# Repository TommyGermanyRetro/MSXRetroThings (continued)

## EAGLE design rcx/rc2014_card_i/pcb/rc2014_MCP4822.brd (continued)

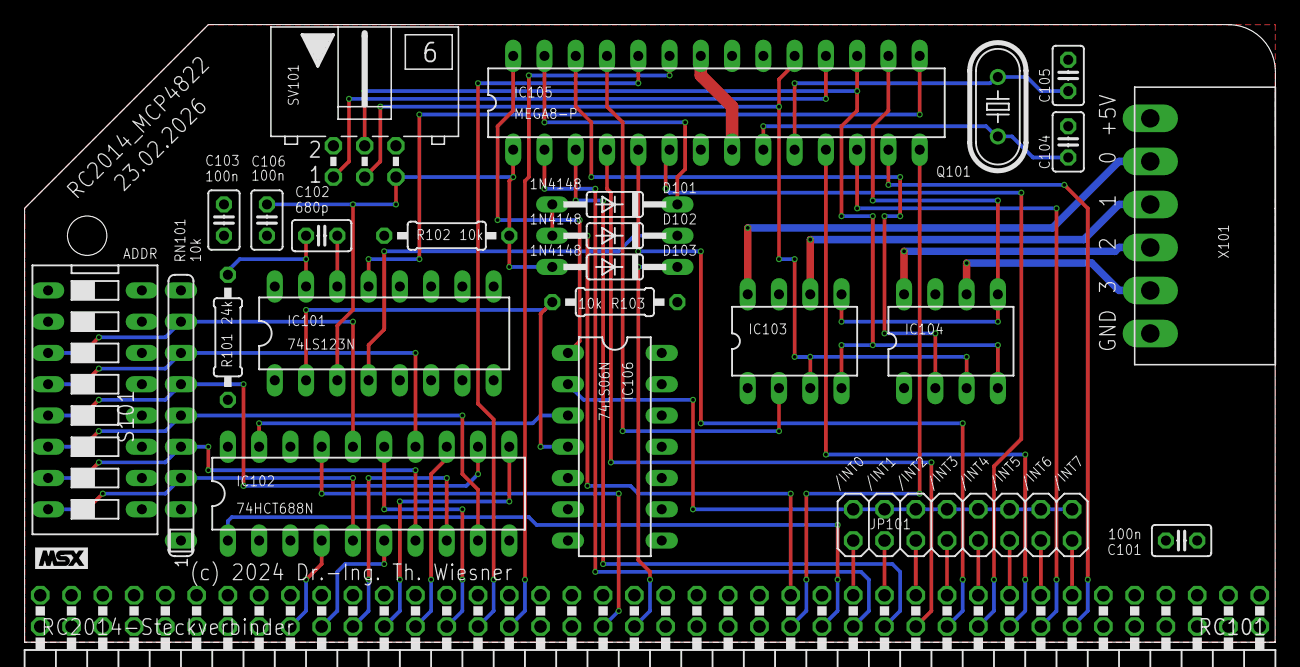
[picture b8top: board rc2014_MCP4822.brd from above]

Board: 2 copper layers, 101.6 x 50.2 mm, 25 parts (0 on the bottom side), 59 nets.

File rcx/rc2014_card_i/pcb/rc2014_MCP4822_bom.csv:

Qty,Reference,Value,Package,Description
1,RC101,RC2014,RC2014-STECKER,"RC2014 enhanced bus connector, pin header 2 x 40, 2.54 mm, angled"
2,"IC103, IC104",MCP4822,DIL08,Dual 12-bit D/A converter with SPI (Microchip MCP4822)
1,IC105,ATmega8,DIL28-3,Microcontroller ATmega8 (firmware not yet in this repository)
1,IC102,74HCT688N,DIL20,8-bit comparator: card address against the DIP switch
1,IC101,74LS123N,DIL16,Dual monostable multivibrator
1,IC106,74LS06N,DIL14,"Hex inverter, open collector"
1,Q101,16MHz,HC49U-V,"Crystal 16 MHz, HC49/U"
2,"C104, C105",27p,C025-025X050,"Ceramic capacitor 27 pF, 2.5 mm pitch"
3,"C101, C103, C106",100n,C025-025X050,"Ceramic capacitor 100 nF, 2.5 mm pitch"
1,C102,680p,C025-025X050,"Ceramic capacitor 680 pF, 2.5 mm pitch"
3,"D101, D102, D103",1N4148,DO35-10,Signal diode
1,R101,24k,0207/10,"Resistor 24 kOhm, axial, 10 mm pitch"
2,"R102, R103",10k,0207/10,"Resistor 10 kOhm, axial, 10 mm pitch"
1,RN101,10k,SIL9,"Resistor network 8 x 10 kOhm, common pin, SIL9"
1,S101,ADDR,DS-08,DIP switch 8 positions: card address
1,SV101,Box header 2x3,ML6L,"Box header 6 pins (2 x 3), 2.54 mm: ISP connector of the ATmega8"
1,X101,AKL182-6,AKL182-6,"Pluggable terminal block 6 pins, 3.5 mm: analog outputs with +5 V and GND"
1,JP101,2X08,2X08,"Pin header 2 x 8, 2.54 mm, with jumper: selects the interrupt line /INT0-/INT7 of the XIO PIC"

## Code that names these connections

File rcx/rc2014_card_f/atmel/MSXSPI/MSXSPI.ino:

//***********************************************************************************************
//* 4x SPI at ATMEGA8                                                                           *
//***********************************************************************************************
//* This sketch uses an ATMEGA8 as driver for four seperate SPI busses with a speed up to 2 MHz *
//***********************************************************************************************
//* File:  MSXSPI.ino                                                                           *
//***********************************************************************************************
//* Changes:                                                                                    *
//* V1.0.0 - 21.10.2026 - base version                                                          *
//***********************************************************************************************

#include <Arduino.h>
#include <SPI.h>
#include <elapsedMillis.h>

// Definition of pin usage

#define SA0         (1 << PC0)   
#define SA1         (1 << PC1)
#define SPIBUS0     (1 << PC2)
#define SPIBUS1     (1 << PC3)
#define SPISS       (1 << PB2)
#define SPIINT      (1 << PC5)
#define SRD         (1 << PB0)
#define SPICS       (1 << PB1)
#define IORDY       (1 << PC4)

// Define cycle for hardware wait steering

elapsedMicros waitTime = 0;

// Define SPI controls

long    freq[4]     = {2000000,1000000,500000,250000};
uint8_t mode[4]     = {SPI_MODE0,SPI_MODE1,SPI_MODE2,SPI_MODE3};

uint8_t mMsg[4]     = {0,0,0,0};
uint8_t mMode[4]    = {0,0,0,0};
uint8_t mClk[4]     = {0,0,0,0};
bool    mChange[4]  = {false,false,false,false};

// Define control signals

uint8_t activeBus   = 0;
uint8_t dMode       = 0;
uint8_t dClk        = 0;
uint8_t dBus        = 0;
uint8_t dCmd        = 0;
uint8_t data        = 0;
uint8_t addr        = 0;
uint8_t wr          = 0;

// SETUP()

void setup() {

  // Start SPI with standard settings

  SPI.begin();
  SPI.beginTransaction(SPISettings(2000000, MSBFIRST, SPI_MODE0));

  // PORT D as databus
  // Starts as input

  DDRD = 0;

  // Activate PullUp at PORT C

  PORTC = 0xFF;

  // Control signals

  DDRC &= ~SA0;
  DDRC &= ~SA1;
  DDRC |= SPIBUS0;
  PORTC &= ~SPIBUS0;
  DDRC |= SPIBUS1;
  PORTC &= ~SPIBUS1;
  DDRC |= IORDY;
  PORTC |= IORDY;
  DDRC |= SPIINT;
  PORTC &= ~SPIINT;
  DDRB &= ~SRD;
  DDRB &= ~SPICS;
  DDRB |= SPISS;
  PORTB |= SPISS;
  
}

// LOOP()

void loop() {

  // Check, if SPI is selected
  
  if(PINB & SPICS) {

    // Take over /WAIT

    PORTC &= ~IORDY;

    // Start cycle measuring

    waitTime = 0;

    // Get direction RD = LOW, WR = HIGH

    wr = PINB & SRD;

    // Get address

    addr = PINC & 0x03;

    // Analyse address

    switch(addr){
      
      // SPI-MODE 1  Bits 7..6 = FREQ   Bits 5..4 = MODE   Bits 3..2 = NC   Bits 1..0 = BUS

      case 0: 

              if (wr){

                data = PIND; 

                dBus = data & 0x03;
                dMode = (data & 0x30) >> 4;
                dClk = (data & 0xc0) >> 6;

                if (dMode!=mMode[dBus]){
                  mMode[dBus] = dMode;
                  mChange[dBus] = true;
                }

                if (dClk!=mClk[dBus]){
                  mClk[dBus] = dClk;
                  mChange[dBus] = true;
                }    

              }
              else {

                DDRD = 0xff;  // PORT D output

                data = activeBus;
                data |= (mMode[activeBus] << 4);
                data |= (mClk[activeBus] << 6);
                
                PORTD = data;                

              }      

      break;

      // SPI-MODE 2   Bits 7..6 = CMD   Bits 5..2 = NC   Bits 1..0 = Bus

      case 1:

              if (wr){

                data = PIND; 
           
                dCmd = (data & 0xc0) >> 6;

                // Set active Bus
 
                if (dCmd == 0) activeBus = data & 0x03;
         
              }
              else {

                DDRD = 0xff;  // PORT D output

                data = activeBus;
                
                PORTD = data;                  

              }

      break;

      // SPI /CS on/off
      
      case 2:

              if (wr){

                data = PIND; 

                if (data > 0){
                  PORTB |= SPISS;
                  SPI_CS_Set(activeBus);
                  PORTB &= ~SPISS;
                }
                else{
                  PORTB |= SPISS; 
                }

              }
              else {

                DDRD = 0xff;  // PORT D output

                data = (PINB & SPISS) >> 2;

                PORTD = data;                  

              }      

      break;

      // SPI-TRANSFER

      case 3:

              // SPI Settings changed?
              // Then restart SPI-Bus

              if (mChange[activeBus]){
                SPI.begin();
                SPI.beginTransaction(SPISettings(freq[mClk[activeBus]], MSBFIRST, mode[mMode[activeBus]]));
                mChange[activeBus] = false;
              }

              // Check for RD (0) or WR (1)
              
              if (wr){

                data = PIND; 

                SPI.transfer(data);
 
              }
              else {

                DDRD = 0xff;  // PORT D output
 
                data = SPI.transfer(0);

                PORTD = data;
                
              } 

      break;

      default:

      break;
    }
  
    // Wait for MVFF to end (74123 has 4700 ns as impulse length) if still active

    while(waitTime<=5);
  
    // Release /WAIT to go on in program

    PORTC |= IORDY;

    // Keep driving the data bus until the read cycle has ended (/RD high again); /WAIT on the
    // bus rises slowly through its pull-up and the CPU takes the data one clock after that

    while (!(PINB & SRD));

    // Port D as Input

    DDRD = 0;
    PORTD = 0;

  }

}

// CS routine on/off

void SPI_CS_Set(uint8_t cs){

    switch(cs){
      case 0:   PORTC &= ~SPIBUS0;
                PORTC &= ~SPIBUS1;
      break;
      case 1:   PORTC |= SPIBUS0;
                PORTC &= ~SPIBUS1;
      break;
      case 2:   PORTC &= ~SPIBUS0;
                PORTC |= SPIBUS1;
      break;
      case 3:   PORTC |= SPIBUS0;
                PORTC |= SPIBUS1;
      break;
      default:
                PORTC &= ~SPIBUS0;
                PORTC &= ~SPIBUS1;
      break;
    }

}

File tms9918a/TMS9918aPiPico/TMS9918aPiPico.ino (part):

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//* 98h/99h, 7 RESET of the MSX, 8TTTTTT time mark (µs, 24 bits, before an access after >= 64 µs).  *
//* A 7 received from the PC resets the MSX.                                                        *
//*                                                                                                 *
//* Pins:  D0-D7 = GP0-GP7, /CSW = GP8, /CSR = GP9, A0 = GP10, /RES = GP11 (input),                 *
//*        VDP = GP12 (input, HIGH while address 98h/99h is present), /RESMSX = GP20 (output),      *
//*        /WAIT = GP21 (output, active LOW)                                                        *
//*                                                                                                 *
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// Pins
//===================================================================================================

static const uint PIN_D0     = 0;                       // D0-D7, /CSW, /CSR, A0 = GP0-GP10
static const uint PIN_RES    = 11;                      // /RES of the MSX (input)
static const uint PIN_VDP    = 12;                      // address 98h/99h (input, active HIGH)
static const uint PIN_RESMSX = 20;                      // reset the MSX (active LOW)
static const uint PIN_WAIT   = 21;                      // /WAIT (active LOW)

static const uint32_t BIT_CSW = 1u << 8;                // bits in the captured value
static const uint32_t BIT_CSR = 1u << 9;
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//===================================================================================================

static const float    PIO_CLOCK_HZ     = 25000000.0f;   // PIO clock (40 ns per instruction)
static const uint     FIFO_STALL_LEVEL = 6;             // /WAIT from this RX FIFO level on
static const uint32_t STALL_MAX_US     = 100;           // longest hold time via /WAIT
static const uint32_t RES_DEBOUNCE_US  = 50;            // /RES must be LOW this long
static const uint32_t MARK_US          = 64;            // interval of the time marks
static const uint32_t RESET_PULSE_MS   = 1;             // length of the reset pulse
static const uint32_t RESET_CHECK_MS   = 1;             // wait time before checking /RES

//===================================================================================================
// Ring buffer core 1 -> core 0
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// Diagnostic counters

static volatile uint32_t countDropped  = 0;             // dropped because the buffer was full
static volatile uint32_t countInvalid  = 0;             // neither /CSW nor /CSR active

//===================================================================================================
// Core 1: PIO, time stamps, /RES
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{
    // Inputs D0-D7, /CSW, /CSR, A0 and VDP without pull resistors

    for (uint pin = PIN_D0; pin <= PIN_VDP; pin++)
    {
        gpio_init(pin);
        gpio_set_dir(pin, GPIO_IN);
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
    // /WAIT: output with idle level HIGH, then handed over to the PIO

    gpio_init(PIN_WAIT);
    gpio_put(PIN_WAIT, 1);
    gpio_set_dir(PIN_WAIT, GPIO_OUT);
    gpio_disable_pulls(PIN_WAIT);

    uint offset = pio_add_program(pio, &vdpsniff_program);
    pio_sm_config c = vdpsniff_program_get_default_config(offset);

    sm_config_set_in_pins(&c, PIN_D0);
    sm_config_set_jmp_pin(&c, PIN_VDP);
    sm_config_set_in_shift(&c, false, false, 32);
    sm_config_set_set_pins(&c, PIN_WAIT, 1);
    sm_config_set_fifo_join(&c, PIO_FIFO_JOIN_RX);
    sm_config_set_mov_status(&c, STATUS_RX_LESSTHAN, FIFO_STALL_LEVEL);
    sm_config_set_clkdiv(&c, (float)clock_get_hz(clk_sys) / PIO_CLOCK_HZ);

    pio_sm_init(pio, sm, offset, &c);
    pio_sm_set_pins_with_mask(pio, sm, 1u << PIN_WAIT, 1u << PIN_WAIT);
    pio_sm_set_consecutive_pindirs(pio, sm, PIN_WAIT, 1, true);
    pio_gpio_init(pio, PIN_WAIT);
    pio_sm_set_enabled(pio, sm, true);

    // /RES of the MSX

    gpio_init(PIN_RES);
    gpio_set_dir(PIN_RES, GPIO_IN);

    core1Ready = true;
}
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
    // /RES: a LOW phase of at least RES_DEBOUNCE_US reports a RESET

    if (gpio_get(PIN_RES))
    {
        resArmed = true;
        resLowStart = 0;
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
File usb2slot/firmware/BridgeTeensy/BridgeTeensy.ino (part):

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//*                                                                                                 *
//* Cycles: memory read (3 T), opcode fetch M1 (4 T + 1 wait cycle + refresh), memory               *
//* write (3 T), I/O read and write (4 T). Before every read cycle the data bus is precharged to    *
//* FFh via the 74HCT245 and released before /RD. /WAIT (pin 4) extends every                       *
//* cycle, by at most 100 ms. With heartbeat monitoring the bridge issues idle refresh between      *
//* cycles and goes to OFF without a heartbeat (like an unpowered MSX).                             *
//*                                                                                                 *
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//*   w<slot> <adr> <value>  memory write             i <port>             I/O read                 *
//*   o <port> <value>       I/O write                <n>*<command>        command n times          *
//*   u / d                  release / assert /RESET  c                    measure CLOCK_IN         *
//*   t <n>                  slow /WAIT by n clocks (test, 0 = off)   jumper pin 29 -> pin 4        *
//*   z <ms>                 heartbeat timeout (0 = no monitoring)                                  *
//*   h / s                  heartbeat (RUN) / status        without heartbeat: OFF                 *
//*   p [ms]                 /RESET pulse (default 10 ms)    q <0|1>  TEST line LOW/HIGH            *
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static const uint8_t PIN_MERQ     = 6;
static const uint8_t PIN_RD       = 9;
static const uint8_t PIN_WR       = 32;
static const uint8_t PIN_IORQ     = 35;
static const uint8_t PIN_M1       = 34;
static const uint8_t PIN_RFSH     = 31;
static const uint8_t PIN_SLTSL1   = 1;
static const uint8_t PIN_SLTSL2   = 0;
static const uint8_t PIN_CS1      = 24;
static const uint8_t PIN_CS2      = 25;
static const uint8_t PIN_CS12     = 28;
static const uint8_t PIN_RESET    = 30;
static const uint8_t PIN_OE_WR    = 2;
static const uint8_t PIN_WAIT     = 4;
static const uint8_t PIN_INT      = 5;
static const uint8_t PIN_TEST     = 29;
static const uint8_t PIN_CLOCK    = 33;
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static const uint32_t G6_CS1    = 1u << 12;
static const uint32_t G6_CS2    = 1u << 13;

// GPIO7: D0-D3 = Bit 0-3, D4-D7 = Bit 16-19, /MERQ = 10, /RD = 11, /WR = 12, /IORQ = 28, /M1 = 29

static const uint32_t G7_DATA = 0x000F000Fu;
static const uint32_t G7_MERQ = 1u << 10;
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static const uint32_t G7_IORQ = 1u << 28;
static const uint32_t G7_M1   = 1u << 29;

// GPIO8: /CS12 = Bit 18, /RFSH = Bit 22, /RESET = Bit 23

static const uint32_t G8_CS12  = 1u << 18;
static const uint32_t G8_RFSH  = 1u << 22;
static const uint32_t G8_RESET = 1u << 23;

// GPIO9: /OE_WR = Bit 4, CLOCK_IN = Bit 5, /WAIT = Bit 6, /INT = Bit 8, TEST = Bit 31

static const uint32_t G9_OE_WR    = 1u << 4;
static const uint32_t G9_CLOCK_IN = 1u << 5;
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
static const uint32_t MEASURE_MS   = 50;                // measuring window for CLOCK_IN
static const uint32_t EDGE_TIMEOUT = 3000;              // CPU clocks until "no clock" (5 us)
static const uint32_t MAX_WAIT_T   = 358000;            // maximum number of inserted wait clocks (100 ms; a Z80
                                                        // waits any length of time, the limit only catches a
                                                        // hanging card)
static const uint32_t MAX_TEST_WAITS = 64;              // maximum number of wait clocks in test mode (t <n>)
static const size_t   LINE_SIZE    = 48;
static const uint32_t RESET_MS     = 10;                // default length of the /RESET pulse
static const uint8_t  PROTOCOL_VERSION = 3;             // version of the binary protocol
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static uint8_t  refreshR    = 0;                        // refresh counter R (7 bits)
static uint8_t  refreshI    = 0;                        // refresh register I
static bool     clockFailed = false;                    // CLOCK_IN did not arrive
static uint32_t testWaits   = 0;                        // test mode: extend /WAIT by this many clocks
static uint32_t superviseMs = 0;                        // heartbeat timeout, 0 = no monitoring
static uint32_t lastRun     = 0;                        // time of the last heartbeat (millis)
static bool     busOn       = true;                     // RUNNING (true) or OFF (false)
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{
    idleOutput(PIN_RESET, LOW);                         // cartridges in reset

    const uint8_t highPins[] = { PIN_MERQ, PIN_RD, PIN_WR, PIN_IORQ, PIN_M1, PIN_RFSH, PIN_SLTSL1,
                                 PIN_SLTSL2, PIN_CS1, PIN_CS2, PIN_CS12, PIN_OE_WR };
    for (uint8_t pin : highPins)
    {
        idleOutput(pin, HIGH);                          // inactive
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    }

    pinMode(PIN_CLOCK_IN, INPUT);
    pinMode(PIN_WAIT, INPUT_PULLUP);
    pinMode(PIN_INT, INPUT_PULLUP);
    idleOutput(PIN_TEST, HIGH);                         // test line to /WAIT, HIGH = no slowdown
}

//===================================================================================================
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        }
        testWaits = waits;
        GPIO9_DR_SET = G9_TEST;
        Serial.printf("test mode: %u wait clocks per cycle (jumper TEST pin 29 -> /WAIT pin 4)\n", waits);
        return;
    }

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static const uint8_t OP_SYNC  = 0x09;
static const uint8_t OP_CFG   = 0x0B;                   // timeout in ms (2)
static const uint8_t OP_TEST  = 0x0C;                   // test line TEST: 0 = LOW, 1 = HIGH
static const uint8_t OP_IOWRW = 0x0D;                   // port, value; response with wait clocks (4)
static const uint8_t OP_MRDNG = 0x0E;                   // slot, adr (2), count (2), distance in clocks

static const uint8_t ST_OK    = 0;
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
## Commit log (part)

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2026-03-14 Initial commit (history cleared)
2026-03-29 First data to RC2014 I2C Base
2026-03-29 Further data
2026-04-05 Various basic code attached
2026-04-05 I2C basic examples attached
